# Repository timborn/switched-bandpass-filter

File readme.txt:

Thu Jul 20 09:18:21 MST 2023
----------------------------
Ron dropped off a couple of pages of hand drawn sketchs to make into a board.

CHANGE REQUESTS
X. change 4-pin header to 6-pin header
    Ron Taylor, 230719 4:47 PM
    Already thought I’d something. Please make it a 6pin header for the 
    switching so we can reference ground and have a spare too. Thanks
    
    tim born, 230719 4:48 PM
    6 pins instead of 4?  got it
2. correct board size appears to be 82x56mm
X. make sure to label Fx in/out on back of board!
4. DRC "solder mask aperture bridges items with different nets"
   SOT89 for 7805 has no solder bridge between pads for SMT part.
   I turned this error into a warning.  Don't know what I can do 
   to actually fix this.
X. fix this: single branch only using master
X. get rid of traces from front that route on the back
7. spread the connections from Fx in/out to U1 further apart
X. may not need full 15mm width for each of the filter runs
   squeeze them in and let Ron inspect
   we basically have a 56mm width minus SMA connectors minus headers
   there just isn't enough for 4*15mm filter strips
   Resolved: just jam them in.  Ron thinks they will fit.
X. increase board size and add mounting holes in the corners.
   3.25mm plated through and grounded, for 4-40 mounting h/w.
X. update board size on PCB viewer
X. traces to SMA are 50 ohm and need to be 3mm
X. add 3mm wide strips between filters by removing solder mask 
    so vertical boards could be soldered on
13. zeroed out "solder mask expansion" and "solder mask minimum web width"
    as I got stern warnings to use zero and let mfgr pick something suitable.
    Need to change the template.

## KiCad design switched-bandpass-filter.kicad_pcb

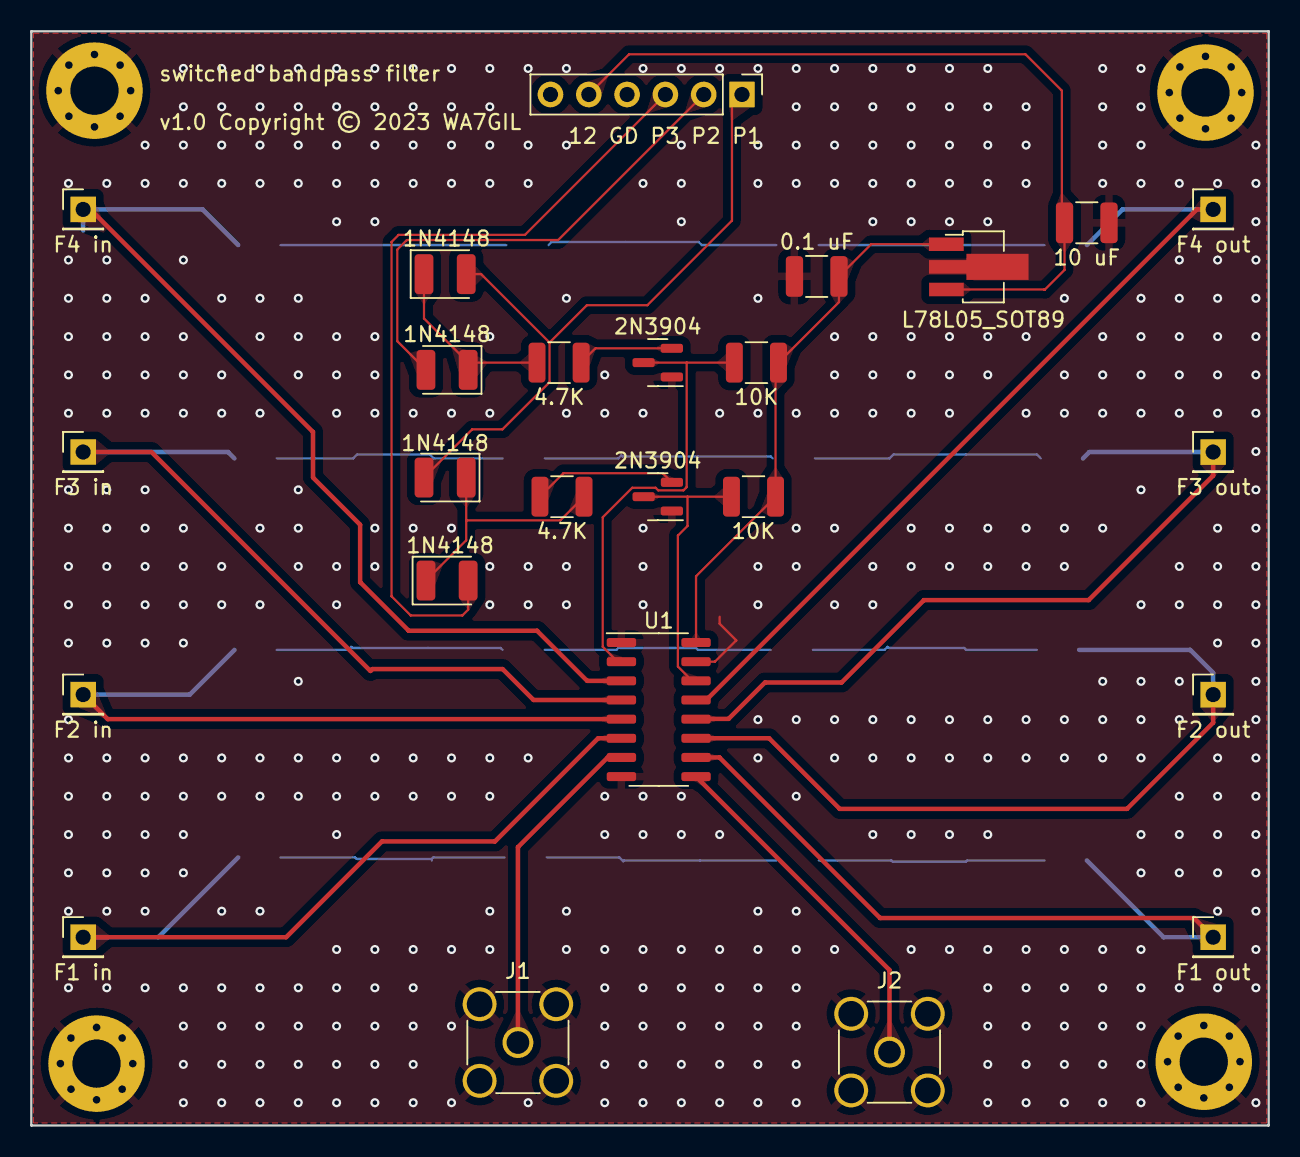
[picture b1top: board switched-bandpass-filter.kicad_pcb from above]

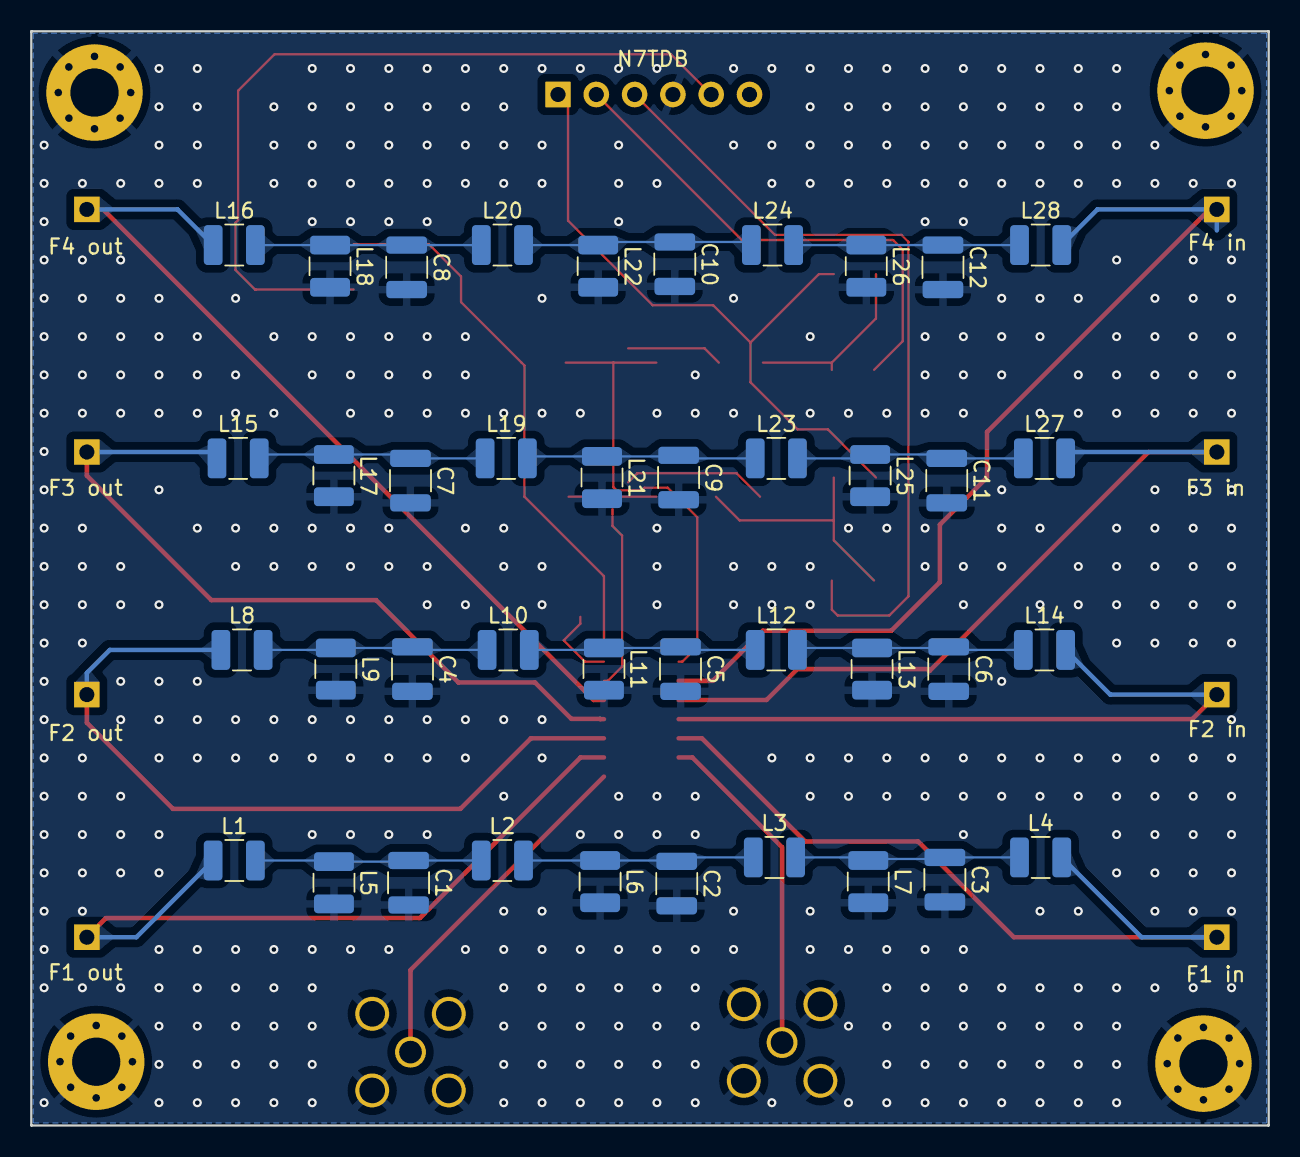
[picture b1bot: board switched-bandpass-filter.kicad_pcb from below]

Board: 2 copper layers, 82.1 x 72.6 mm, 69 parts (40 on the bottom side), 34 nets.

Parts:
C1, C2, C3, C4, C5, C6, C7, C8, C9, C10, C11, C12: C_1210_3225Metric
C13: 0.1 uF; C_1210_3225Metric
C14: 10 uF; C_1210_3225Metric
D9, D10, D11, D12: 1N4148; D_1210_3225Metric
H1, H2, H3, H4: MountingHole_3.2mm_M3_Pad_Via
J1, J2: SMA; SMA_Amphenol_901-144_Vertical
J3: F4 in; PinHeader_1x01_P2.54mm_Vertical
J4: PinHeader_1x06_P2.54mm_Vertical
J5: F3 in; PinHeader_1x01_P2.54mm_Vertical
J6: F2 in; PinHeader_1x01_P2.54mm_Vertical
J7: F1 in; PinHeader_1x01_P2.54mm_Vertical
J8: F1 out; PinHeader_1x01_P2.54mm_Vertical
J9: F2 out; PinHeader_1x01_P2.54mm_Vertical
J10: F3 out; PinHeader_1x01_P2.54mm_Vertical
J11: F4 out; PinHeader_1x01_P2.54mm_Vertical
L1, L2, L3, L4, L5, L6, L7, L8, L9, L10, L11, L12, L13, L14, L15, L16, L17, L18, L19, L20, L21, L22, L23, L24, L25, L26, L27, L28: L; L_1210_3225Metric
Q5, Q6: 2N3904; SOT-23
R9, R10: 4.7K; R_1210_3225Metric
R11, R12: 10K; R_1210_3225Metric
U1: FST3253MX; SOIC-16_3.9x9.9mm_P1.27mm
U2: L78L05_SOT89; SOT-89-3_Handsoldering

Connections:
+5V: C13.1, R11.2, R12.2, U1.16, U2.1 (OUT)
+12V: C14.1, J4.5, U2.3 (IN)
F1 common: J1.1 (In), U1.7
F1 in: J7.1, L4.2, U1.6
F1 out: J8.1, L1.1, U1.10
F2 common: J2.1 (In), U1.9
F2 in: J6.1, L14.2, U1.5
F2 out: J9.1, L8.1, U1.11
F3 in: J5.1, L27.2, U1.4
F3 out: J10.1, L15.1, U1.12
F4 in: J3.1, L28.2, U1.3
F4 out: J11.1, L16.1, U1.13
GND: C1.2, C2.2, C3.2, C4.2, C5.2, C6.2, C7.2, C8.2, C9.2, C10.2, C11.2, C12.2, C13.2, C14.2, H1.1, H2.1, H3.1, H4.1, J1.2 (Ext), J2.2 (Ext), J4.4, L5.2, L6.2, L7.2, L9.2, L11.2, L13.2, L17.2, L18.2, L21.2, L22.2, L25.2, L26.2, Q5.1 (E), Q6.1 (E), U1.1, U1.8, U1.15, U2.2 (GND)
unnamed: C1.1, L1.2, L2.1, L5.1
unnamed: C2.1, L2.2, L3.1, L6.1
unnamed: C3.1, L3.2, L4.1, L7.1
unnamed: C4.1, L8.2, L9.1, L10.1
unnamed: C5.1, L10.2, L11.1, L12.1
unnamed: C6.1, L12.2, L13.1, L14.1
unnamed: C7.1, L15.2, L17.1, L19.1
unnamed: C8.1, L16.2, L18.1, L20.1
unnamed: C9.1, L19.2, L21.1, L23.1
unnamed: C10.1, L20.2, L22.1, L24.1
unnamed: C11.1, L23.2, L25.1, L27.1
unnamed: C12.1, L24.2, L26.1, L28.1
unnamed: D9.1 (K), D10.1 (K), R9.1
unnamed: D11.1 (K), D12.1 (K), R10.2
unnamed: Q5.2 (B), R9.2
unnamed: Q6.2 (B), R10.1
P1: D9.2 (A), D11.2 (A), J4.1
P2: D10.2 (A), J4.2
P3: D12.2 (A), J4.3
S0: Q6.3 (C), R12.1, U1.14
S1: Q5.3 (C), R11.1, U1.2

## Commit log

2023-07-20 added Rons sketches and a start of a readme.txt with change requests
2023-07-20 made a start on schematic, and ERC passes
2023-07-20 added power supply schematic, and deleted the -backups folder
2023-07-20 added filter ckt, passes ERC, bumped to v0.2, ready for board layout
2023-07-21 v0.2 passes ERC & DRC except for no solder mask between pads on SOT89
2023-07-21 added pdfs to docs/ for v02
2023-07-22 v0.3 added all four filters. ERC pass, DRC struggling. Need a ground plane
2023-07-22 v0.3 ERC pass, DRC two unconnected. Stitching ground planes may solve this.
2023-07-22 v0.3 ERC/DRC pass; via stitch in place. Time for a squint
2023-07-23 v0.4 ERC/DRC pass; added missing caps; mounting holes; moved SMA & headers out and re-spaced filter chains
2023-07-23 starting on v0.5
2023-07-23 v0.5 SMA traces now 0.3mm for 50 ohms
2023-07-23 removed stitched ground plane and shifted filter #3 to make space for 3mm gap in silk screen
2023-07-23 slowly approaching cutting out 3mm strips from solder mask on rear
2023-07-23 many of the FAB markings wanted to be silkscreen, and visaversa
2023-07-23 v0.5 ATP; 3mm wide strips between filters; 3mm traces to SMA
2023-07-23 supress display of 1x1 headers for Fx in/out. Had to supress warnings from DRC as well, since selected component no longer matches what is displayed. It is intended to be an empty plated through hole.
2023-07-23 v1.0 shipped to PCBWay
2023-07-23 tidy up

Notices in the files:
switched-bandpass-filter.kicad_pcb:
Copyright © 2023 Ron Taylor WA7GIL
v1.0 Copyright © 2023 WA7GIL
